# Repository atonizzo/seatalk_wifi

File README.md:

# <p align=center>SEATALK_WIFI</p>

---
### Table of contents
1. [Introduction](#introduction)
2. [Hardware](#hardware)
    1. [Schematic](#schematic)
        1. [Serial Bridge](#serial_bridge)
    2. [PCB Layout](#pcb_layout)
        1. [Front Side](#front_side)
        2. [Back Side](#back_side)
3. [Software](#software)
    1. [Configuration via Web Page](#web_page)
        1. [Programming Over the Air](#ota_programming)
        2. [Configuration for Wind Instrument](#wind_instrument)
    2. [Serial Logger](#serial_logger)
    3. [Telnet Logger](#telnet_logger)
    4. [NMEA Server](#nmea_server)
        1. [NMEA Talker](#nmea_talker)
    5. [Software Debug Port](#debug_port)
    6. [Integration with SignalK](#signalk)
    7. [Wind Gauges](#wind_gauges)
4. [Further Development](#further_development)
5. [Holder for ST40 devices](#st40_holder)
5. [Contact](#contact)
---

#  Introduction
The hardware and the included software of this project create a
bridge between a Raymarine SeaTalk1 instrument and NMEA. The NMEA
sentences generated are sent via a WiFi connection to a remote
client. This connection can be directly used with chart plotters such as
[OpenCPN](https://opencpn.org/).

The advantages of this solution are:

- Allows older instrumentation using SeaTalk1 to be connected to newer
chartplotters receiving NMEA sentences via WiFI
- The WiFi link allows the instrumentation to be installed in
out-of-the-way location thus freeing space in the navigation area
- The board can be installed very close to the data source and does not
require laying out data cables to a chart plotter. All that is needed
is a 12 Volt connection to the battery

#  Hardware
The hardware is a simple board with pads designed to connect to to a 12V
source on one side (typically a switched and fused boat battery) and to
a Seatalk connector on the other (see [PCB layout pictures](#pcb_layout))
board supplies 12V to power the target instrument so that the only
connection needed for the system to work is a single 12V feed from the boat
electrical panel.

The hardware board is not fused. It is expected that a 0.1A fast acting fuse
be provided on the 12V supply line immediately before the circuit. The 12V feed
that powers the circuit should also be fused at the distribution panel
or go through an appropriately sized resettable circuit breaker.

##  Schematic

During the development of the circuit it was noticed that the Raymarine
instrument being used (an ST40 wind instrument) was very sensitive about
loading of the SeaTalk serial line. To isolate the SeaTalk data line from
the rest of the circuitry Q2 acts as a buffer.

Q2 also inverts the polarity of the signal. The polarity is once again inverted
by the receiver integrated into U3, which also provides voltage translation
down to 3.3V.

U1 implements a regulator rated to least 2A. An earlier version of this board
designed with a linear regulator showed that the regulator tended to overheat,
which prompted a redesign using a switching topology.

###   Serial Bridge
R12 allows the board to be used as a receive-only serial to WIFI bridge. In
order to use this feature, the changes to the schematic are:

| Remove | Install |
| :---:  | :---:   |
| Q1, Q2, R9    | R12     |

Now the center pad can be connected to the TX pin of the RS232 port of a
NMEA device and the serial stream of NMEA sentences can be sent out to
WIFI.

##  PCB Layout

The board has been designed using KiCad and the fabrication files are provided
in the ```fab``` directory.

Board dimensions are 31 mm x 22 mm.

###  Front Side

On the right side of the board the pads, from top to bottom, are:

- GND
- 12V (unfused, use a 500mA inline fuse)

These pads are connected to the boat battery. A better installation
would require powering this board from the same switched connection
that powers the navigation station.

On the left side of the board the pads are meant to be connected to a
Raymarine SeaTalk instrument. A SeaTalk1 cable has 3 wires that are
color coded and the typical color of the insulating jacket is shown
in the list. From top to bottom:

| Function    | Jacket Color       |
| :---:       | :---:              |
| GND         | black or bare wire |
| SeaTalk     | yellow             |
| +12V        |  red               |

On the top side of the board the pads, from left to right, are:

- Serial Logger (unmarked on the PCB) This pin is connected to the TX pin
of serial port 2 of the ESP12 and -if enabled by the user- emits a
pretty print of all the commands handled by the hardware
(see [Serial Logger](#serial_logger))

- Programming cable RX line (marked with R in the layout). This is connected
to the RX pin of serial port 1 of the ESP12 and is primarily used to program
the device. Serial port 1 of the ESP12 device is used for both programming
the board as well as to receive the SeaTalk sentences from the instrument.
During development this means that this pin must be disconnected from the
programming cable before resetting the board to prevent interference between
the programmer hardware and the SeaTalk instrument. Failure to disconnect
this cable during regular use will prevent the SeaTalk sentences from
being received by the MCU

- Programming cable TX line (marked with T in the layout) is connected to the
TX pin of the ESP12 and is mainly used during programming. It can also be
used to output general purpose debug information but the terminal must be
programmed with the same serial parameters used by SeaTalk, which are
usually 4800 bauds, 8 bits, Even parity, 1 Stop bit.

Since the board power supply is 3.3V the typical programming is performed with a
USB to serial converter connected to pads R, T and GND. If no further software
development is expected the programming cable should be disconnected from the
board and the pads left unconnected.

###  Back Side

The two switches on the left side of the image are only used to program the
board when using the serial port. Once the initial firmware image is programmed
the OTA facility (see [Programming Over the Air](#ota_programming))
can then be used to reimage the flash memory thus not requiring neither the
serial port nor the toggling of the switches.

In order to program the board the RST switch (the top one in the picture)
should be pulsed **while the BOOT switch is kept pressed**. At this point
the board is ready for the programmer to write the new software.

#  Software
The software can be compiled using the Arduino GUI. The only library required
is Lennart Henning's ESPTelnet library which is used for the
both the Telnet server and the NMEA server.

##  Configuration via Web Page
The software runs a web server that serves a single web page used
to configure a few parameters of the bridge. Among other things the page allows
setting the output power for the WiFi transmitter, enabling or disabling
of the serial and telnet logging windows and the port
at which the NMEA server is listening. During the first start the software
creates a configuration space in EEPROM and stores a few default parameters.
The defaults have been chosen to aid in the debgging of the board during firts
installation and can be changed accordingly after full operation has been
achieved. The built in defaults are:

- Serial logger enabled
- Telnet logger enabled
- The default primary NMEA port is 3030
- The default NMEA talker is "LR"
- Activity LED enabled
- OTA programming enabled

An example of the web page is shown in the following picture.

The default hostname for the instrument is "wind" and can be changed in the
software before programming (see [sw/seatalk_wifi.h](sw/seatalk_wifi.h))
or at a later point via the configuration web page.

The bottom of the web page also lists the SeaTalk sentences that are supported
by the firmware programmed on the brige.

###  Programming Over the Air
In order to upgrade the firmware it is convenient to use the "Over the Air"
(OTA) facility of the ESP8266. Once enabled by using the checkbox in the web
page and once the hardware has been reset, a new hostname is available, which
is the device hostname with the "_ota" string appended. For example, if the
device hostname is "wind", the OTA programmer will be available at the hostname
"wind_ota". Now the Arduino IDE or the appropriate Python script can be used
to flash a new image without the need to connect a USB to serial port converter.
Once the new firmware has been written the OTA programming can safely be disabled.

###  Configuration for Wind Instrument
In gusty wind conditions the wind angle -and to a lesser extent the speed- returned
by the wind instrument are subject to very quick jumps only to then return to
prevailing conditions. To filter out some of the noise introduced by these
jumps the angle and speed data can be independently processed by a simple
moving average filter. When these filters are enabled their lenght
can be configured using the web page in the fieldset specific to the wind
instrument.

##  Serial Logger
A timestamped pretty print of all the commands handled by the bridge is
printed out to the serial logger, connected to Serial1 (for wiring information
see [Front Side](#front_side)). This is not the actual NMEA
data but rather descriptive information of each Seatalk command in the
order that it was processed.

In the log -and assuming the coloring is enabled- the command byte is typically
printed in blue, the payload in the regular terminal color, the name of the
command in green and the arguments in terminal color.

Errors are also logged. In this case the byte that caused the error is shown
in red. If any error occurs the entire packet received up until that moment
is tossed and the software will start seeking another command to interpret.
There are 3 types of errors:

- Unrecognized commands, which are commands with the parity bit set but
that are not among those recognized by the software
- Parity violations, where a payload byte was received with the parity
bit set
- Framing violations, where one of the payload bytes was received that
was not consistent with the command being handled.

In the latter 2 cases the argument column provides information about
the offending byte.

##  Telnet Logger
The software runs a Telnet server that outputs a pretty print of all the
commands received, exactly the same information that can be output on the
serial port.

##  NMEA Server
The NMEA sentences are available at the port selected in the settings and
can be accessed directly via the communication configuration of
chartplotters such as [OpenCPN](https://opencpn.org/). The software
will send NMEA data to either NMEA ports as long as there is a connection.

There is a secondary NMEA server that serves the exact same content as
the primary and it can be connected at the primary port number plus one.

###  NMEA Talker
The NMEA talker can be selected through the web page configuration.
The default talker, written in EEPROM upon first boot, is "LR".

##  Software Debug Port
Since the Serial TX line of the programming cable (UART0_TXD in the schematic)
is not shared with SeaTalk it is used to send out debug information that is
useful during installation. To see the output of this port the terminal should
be configured with the same setting as SeaTalk (8 bit, Even parity, 1 Stop bit).
The information output shows the content of the configuration EEPROM as well
as the output from the connection to a WiFi network.

##  Integration with SignalK
Wind speed and direction can be optionally sent to SignalK via a UDP connection.
In the case of the wind instrument the following keys, in the form of serialized
JSON objects, are forwarded to SignalK:

`environment/wind/angleApparent`

`environment/wind/speedApparent`

The source for these keys is set by the firmware to be `Raymarine ST40 Wind`.

To read these keys SignalK must be set to receive a UDP connection from the
seatalk_wifi device. The IP address and port of the SignalK server can be
programmed into the seatlk_wifi device via the
[Configuration Web Page](#web_page).

##  Wind Gauges
In the case in which a connection to a display unit (e.g. OpenCPN or or
SignalK) is not available wind information can be read by means of a pair of
gauges available at the URL http://wind/gauges. This is useful in the case
where a cellphone or a pad is the only device available.

The gauges are updated every second with measured wind speed and direction. The
data is also accumulated and a temperature encoded histogram is created around
the edge of both dials. In this way it is possible to evaluate prevalent
wind condition for the past few minutes.

The Javascript implementation for the gauges was written by Mykhailo Stadnyk
and it is under a MIT license. The GitHub repository can be found at
[Canvas Gauges](https://github.com/Mikhus/canvas-gauges).

#  Further Developmnent
The project can be improved in a number of ways.

## Handling Additional SeaTalk Sentences
The only instrument available during development was an ST40 wind instrument and
the messages that are emitted by that instrument are the only one currently
recognized by the software. The software processes the Seatalk sentences using
a state machine and it makes rather trivial job to add code that handles new
sentences.

## Adding the Ability to Transmit SeaTalk Sentences
The current release does not allow transmitting of Seatalk sentences because
there was no need for it in the only ST40 instrument used for development.

In receive mode, the parity bit is extracted using a technique that involves
checking for RX errors and then assuming that any such error is due to parity
violation (this is required by the way errors are handled in the serial library
of the ESP8266 device), but when sending data the parity bit has to be handled
as a 9th bit independent of the others which makes it impossible to use the
hardware serial port TX pin to do this. When configured to use serial parity
the ESP8266 core sets parity based on the bit pattern to send and does not allow
independently setting the value of the parity bit. For this reason the SeaTalk
TX line is connected to a GPIO in the expectation that a the TX signal can be
bit-banged out of it.

Since SeaTalk is a multiple access protocol the ability to transmit sentences
requires the need to detect possible interfence from other instruments trying
to talk over each other. Since the SeaTalk line is a single one, the
transmitted data is also received back by the bridge, which can compare it
with the data transmitted to detect collisions.

#  Holder for ST40 devices
With the NMEA data now sent via WiFI the ST40 device can optionally be
installed in a more secluded place, clearing up some space in the navigation
station. A 3D printed mount allows installing the bridge PCB behind the
instrument itself and holding the instrument in place with an M3x8
pinch cap screw.

The board is hidden underneath a lid, secured with 2 M2x6 screws, with
power supply wires entering from the bottom and wires to the instrument
coming out from the top.

Original FreeCAD file and STEP files are provided in the ```holder```
directory.

The mounting holes for the holder are 25 mm apart and are spaced to optionally
connect to a DIN rail clip using 3 mm flathead countersunk screws.

#  Contact
<atonizzo@gmail.com>

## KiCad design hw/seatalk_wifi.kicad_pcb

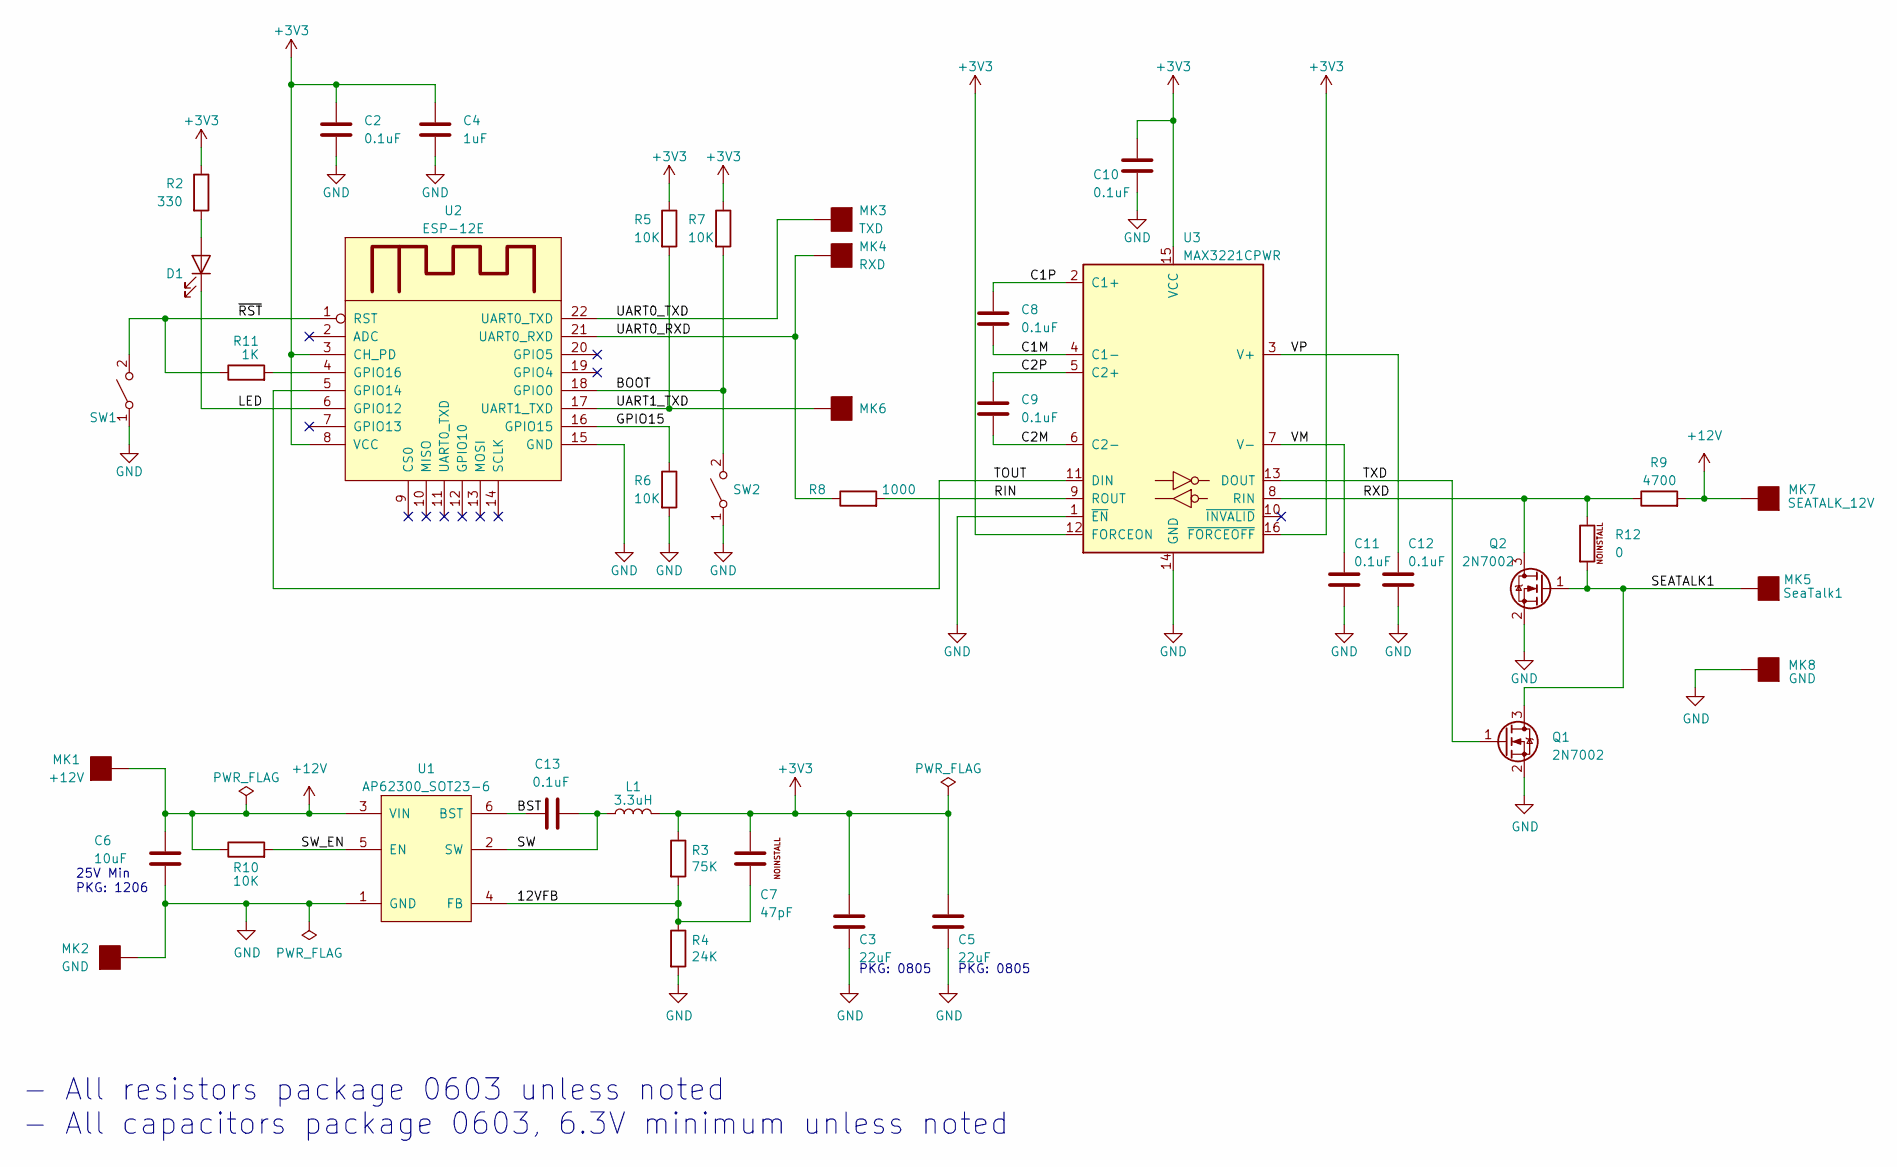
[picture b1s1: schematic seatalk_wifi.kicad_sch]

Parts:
C2, C8, C9, C10, C11, C12, C13: 0.1uF; C_0603_1608Metric; Voltage N/A; Tolerance N/A; MPN N/A; Digikey PN N/A
C3, C5: 22uF; C_0805_2012Metric; Voltage N/A; Tolerance N/A; MPN N/A; Digikey PN N/A
C4: 1uF; C_0603_1608Metric; Voltage N/A; Tolerance N/A; MPN N/A; Digikey PN N/A
C6: 10uF; C_1206_3216Metric; Voltage N/A; Tolerance N/A; MPN N/A; Digikey PN N/A
C7: 47pF; C_0603_1608Metric; Voltage N/A; Tolerance N/A; MPN N/A; Digikey PN N/A
D1: LED_A1K2; LED_0603_1608Metric; MPN N/A; Digikey PN N/A
L1: 3.3uH; INDC3225X120N; MPN N/A; Digikey PN N/A
MK1: +12V; TestPoint_Pad_3.0x3.0mm
MK2, MK8: GND; TestPoint_Pad_3.0x3.0mm
MK3: TXD; TestPoint_Pad_2.0x2.0mm
MK4: RXD; TestPoint_Pad_2.0x2.0mm
MK5: SeaTalk1; TestPoint_Pad_3.0x3.0mm
MK6: UART1; TestPoint_Pad_2.0x2.0mm
MK7: SEATALK_12V; TestPoint_Pad_3.0x3.0mm
Q1, Q2: 2N7002; SOT23-3; MPN 2N7002-G; Digikey PN TBA
R2: 330; R_0603_1608Metric; Tolerance N/A; MPN N/A; Digikey PN N/A
R3: 75K; R_0603_1608Metric; Tolerance N/A; MPN N/A; Digikey PN N/A
R4: 24K; R_0603_1608Metric; Tolerance N/A; MPN N/A; Digikey PN N/A
R5, R6, R7, R10: 10K; R_0603_1608Metric; Tolerance N/A; MPN N/A; Digikey PN N/A
R8: 1000; R_0603_1608Metric; Tolerance N/A; MPN N/A; Digikey PN N/A
R9: 4700; R_0603_1608Metric; Tolerance N/A; MPN N/A; Digikey PN N/A
R11: 1K; R_0603_1608Metric; Tolerance N/A; MPN N/A; Digikey PN N/A
R12: 0; R_0603_1608Metric; Tolerance N/A; MPN N/A; Digikey PN N/A
SW1, SW2: SW_SPST; ADTSM31NV
U1: AP62300_SOT23-6; SOT23-6; MPN AP62300WU-7; Digikey PN 31-AP62200TWU-7TR-ND
U2: ESP-12E; MPN ESP-12E; Digikey PN N/A
U3: MAX3221CPWR; TSSOP-16_4.4x5mm_P0.65mm; MPN MAX3221CPW; Digikey PN 296-26143-5-ND

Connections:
+3V3: C2.1, C3.1, C4.1, C5.1, C7.1, C10.1, L1.1, R2.1, R3.1, R5.1, R7.1, U2.3 (CH_PD), U2.8 (VCC), U3.12 (FORCEON), U3.15 (VCC), U3.16 (~FORCEOFF)
+12V: C6.1, MK1.1, MK7.1, R9.2, R10.1, U1.3 (VIN)
/12VFB: C7.2, R3.2, R4.1, U1.4 (FB)
/BOOT: R7.2, SW2.2 (B), U2.18 (GPIO0)
/BST: C13.1, U1.6 (BST)
/C1M: C8.2, U3.4 (C1-)
/C1P: C8.1, U3.2 (C1+)
/C2M: C9.2, U3.6 (C2-)
/C2P: C9.1, U3.5 (C2+)
/GPIO15: R6.1, U2.16 (GPIO15)
/LED: D1.2 (K), U2.6 (GPIO12)
/RIN: R8.2, U3.9 (ROUT)
/RXD: Q2.3 (D), R9.1, R12.1, U3.8 (RIN)
/SEATALK1: MK5.1, Q1.3 (D), Q2.1 (G), R12.2
/SW: C13.2, L1.2, U1.2 (SW)
/SW_EN: R10.2, U1.5 (EN)
/TOUT: U2.5 (GPIO14), U3.11 (DIN)
/TXD: Q1.1 (G), U3.13 (DOUT)
/UART0_RXD: MK4.1, R8.1, U2.21 (UART0_RXD)
/UART0_TXD: MK3.1, U2.22 (UART0_TXD)
/UART1_TXD: MK6.1, R5.2, U2.17 (UART1_TXD)
/VM: C11.1, U3.7 (V-)
/VP: C12.1, U3.3 (V+)
/~RST: R11.1, SW1.2 (B), U2.1 (RST)
GND: C2.2, C3.2, C4.2, C5.2, C6.2, C10.2, C11.2, C12.2, MK2.1, MK8.1, Q1.2 (S), Q2.2 (S), R4.2, R6.2, SW1.1 (A), SW2.1 (A), U1.1 (GND), U2.15 (GND), U3.1 (~EN), U3.14 (GND)
unnamed: D1.1 (A), R2.2
unnamed: R11.2, U2.4 (GPIO16)

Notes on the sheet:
PKG: 0805
- All resistors package 0603 unless noted - All capacitors package 0603, 6.3V minimum unless noted
25V Min PKG: 1206

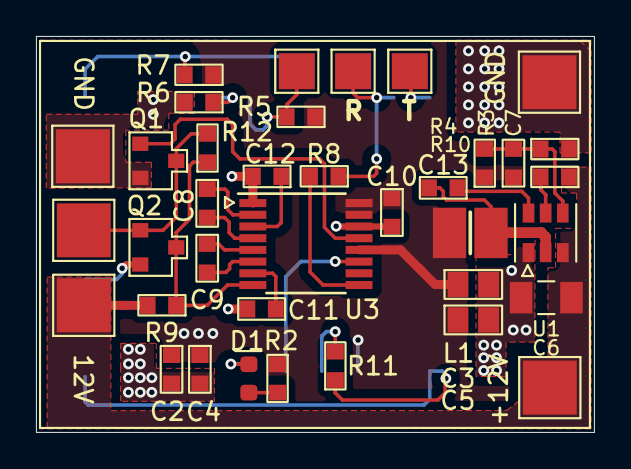
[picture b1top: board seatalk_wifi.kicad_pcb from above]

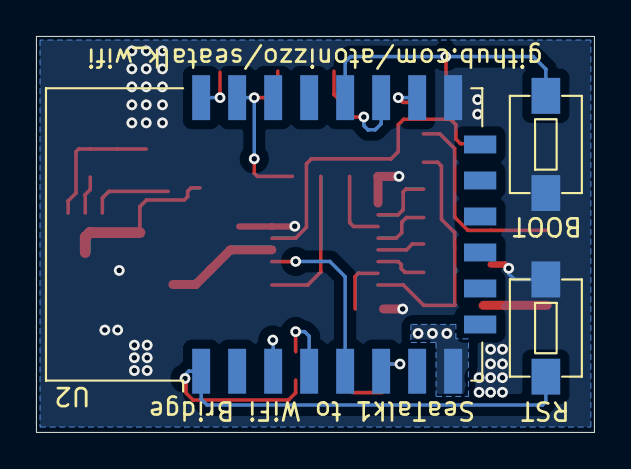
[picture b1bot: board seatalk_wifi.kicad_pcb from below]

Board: 2 copper layers, 31.0 x 22.0 mm, 40 parts (3 on the bottom side), 27 nets.

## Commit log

2022-08-07 Added HW and SW directoires with entire project files.
2022-08-13 Corrected bug in the wind direction sentence and others - Corrected a bug the caused wrong values to be reported for wind direction - Corrected a pretty printing issue - Better sanity check of the pa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
2022-08-15 Minor improvements to README.md file.
2022-08-15 Added activity LED and updated documentation.
2022-08-15 Added R12 which allows an RS232 to WiFi bridge function.
2022-08-15 Updated fab files to include R12.
2022-08-16 Final changes to PCB layout and updated picture of schematic.
2022-08-16 Better handling of WiFi credentials.
2022-08-20 UART0_TXD now used for debug output. Added 3D files for holder.
2022-08-31 Wind moving averages and code cleanup - Added moving averages for wind angle and speed - Cleaned up web page code - Sped up EEPROM update - Corrected the prettyprint of parity, framing and unrecogniz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
2022-09-02 NMEA talker and secondary NMEA server. - The NMEA talker can now be set by the user - Added a secondary NMEA server - Added TOC to README.MD
2022-09-04 Eliminated a code refuse and updated documentation.
2022-09-07 Added WiFi power settings.
2022-09-07 Schematic chenged to reflect the voltage of input caps.
2022-09-07 Fixed a minor issue with web page update.
2022-10-19 New holder design.
2023-03-19 Improvements to web page. SignalK integration. New holder design.
2023-03-19 New PDF schematic file. Updated SVG schematic.
2023-03-22 Cleaned up Markdown lonks in README document.
